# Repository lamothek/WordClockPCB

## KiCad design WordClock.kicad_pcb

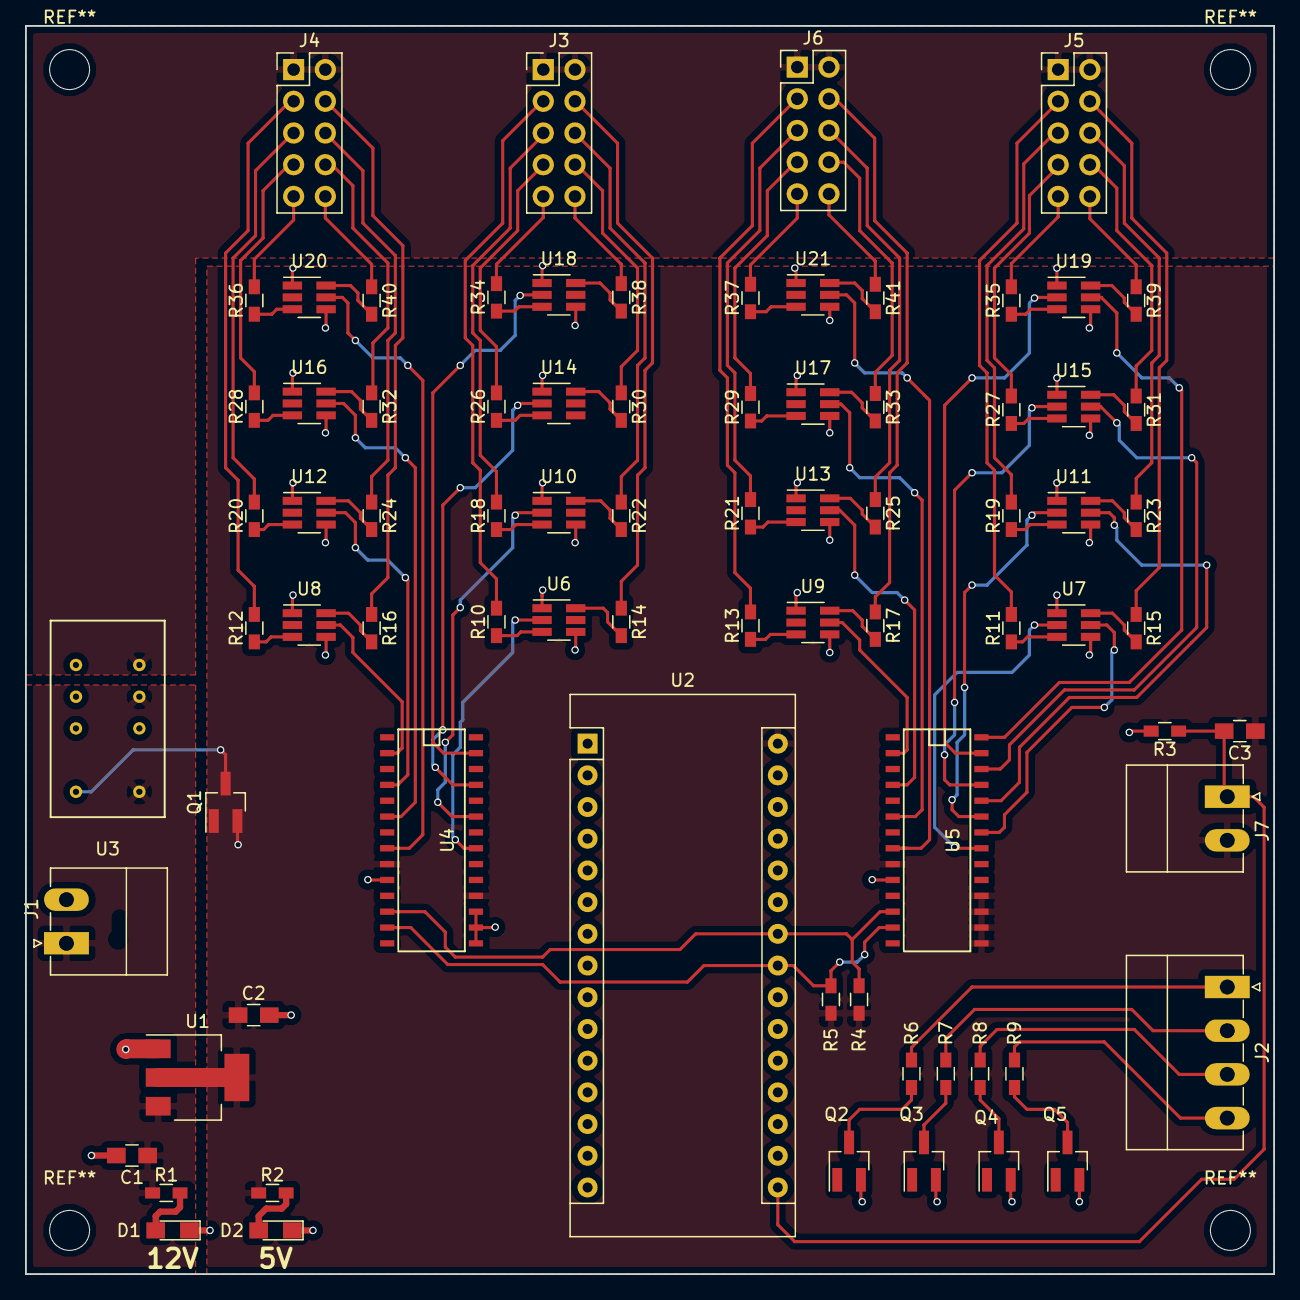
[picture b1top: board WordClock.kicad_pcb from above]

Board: 2 copper layers, 100.0 x 100.0 mm, 79 parts (0 on the bottom side), 119 nets.

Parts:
C1, C2: 4.7uF; C_0805_HandSoldering
C3: 100nF; C_0805_HandSoldering
D1, D2: LED; LED_0805_HandSoldering
J1, J7: Conn_01x02; PhoenixContact_MC-G_02x3.50mm_Angled
J2: Conn_01x04; PhoenixContact_MC-G_04x3.50mm_Angled
J3, J4, J5, J6: Conn_02x05_Top_Bottom; Pin_Header_Straight_2x05_Pitch2.54mm
Q1, Q2, Q3, Q4, Q5: Q_NMOS_GSD; SOT-23_Handsoldering
R1, R2: 1K; R_0603_HandSoldering
R3, R6, R7, R8, R9: 10K; R_0603_HandSoldering
R4, R5: 4.7K; R_0603_HandSoldering
R10, R11, R12, R13, R14, R15, R16, R17, R18, R19, R20, R21, R22, R23, R24, R25, R26, R27, R28, R29, R30, R31, R32, R33, R34, R35, R36, R37, R38, R39, R40, R41: 2.7K; R_0603_HandSoldering
U1: AP1117-50; SOT-223-3_TabPin2
U2: ARDUINO_NANO; Arduino_Nano
U3: E2C-12NU; EC2-12NU
U4, U5: MCP23017; SOIC-28
U6, U7, U8, U9, U10, U11, U12, U13, U14, U15, U16, U17, U18, U19, U20, U21: NUD3124; SOT-23-6_Handsoldering

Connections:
+5V: C2.1, C3.1, J7.2, R2.1, R4.1, R5.1, U1.2, U2.30, U4.9, U4.18, U5.9, U5.15, U5.16, U5.17, U5.18
+12V: C1.1, J1.1, R1.1, U1.3, U3.1, U3.4
ButtonRead: C3.2, J7.1, R3.1, U2.16
GND: C1.2, C2.2, D1.1, D2.1, J1.2, Q1.2, Q2.2, Q3.2, Q4.2, Q5.2, R3.2, U1.1, U2.4, U2.29, U4.10, U4.15, U4.16, U4.17, U5.10, U6.1, U6.4, U7.1, U7.4, U8.1, U8.4, U9.1, U9.4, U10.1, U10.4, U11.1, U11.4, U12.1, U12.4, U13.1, U13.4, U14.1, U14.4, U15.1, U15.4, U16.1, U16.4, U17.1, U17.4, U18.1, U18.4, U19.1, U19.4, U20.1, U20.4, U21.1, U21.4
LED1: J3.3, R10.2
LED2: J3.4, R14.1
LED3: J3.5, R18.2
LED4: J3.6, R22.1
LED5: J3.7, R26.2
LED6: J3.8, R30.1
LED7: J3.9, R34.2
LED8: J3.10, R38.1
LED9: J4.3, R12.2
LED10: J4.4, R16.1
LED11: J4.5, R20.2
LED12: J4.6, R24.1
LED13: J4.7, R28.2
LED14: J4.8, R32.1
LED15: J4.9, R36.2
LED16: J4.10, R40.1
LED17: J5.3, R11.2
LED18: J5.4, R15.1
LED19: J5.5, R19.2
LED20: J5.6, R23.1
LED21: J5.7, R27.2
LED22: J5.8, R31.1
LED23: J5.9, R35.2
LED24: J5.10, R39.1
LED25: J6.3, R13.2
LED26: J6.4, R17.1
LED27: J6.5, R21.2
LED28: J6.6, R25.1
LED29: J6.7, R29.2
LED30: J6.8, R33.1
LED31: J6.9, R37.2
LED32: J6.10, R41.1
LED_PWR: J3.1, J3.2, J4.1, J4.2, J5.1, J5.2, J6.1, J6.2, U3.5
unnamed: D1.2, R1.2
unnamed: D2.2, R2.2
unnamed: Q1.3, U3.12
unnamed: Q2.3, R6.2
unnamed: Q3.3, R7.2
unnamed: Q4.3, R8.2
unnamed: Q5.3, R9.2
unnamed: R10.1, U6.3
unnamed: R11.1, U7.3
unnamed: R12.1, U8.3
unnamed: R13.1, U9.3
unnamed: R14.2, U6.6
unnamed: R15.2, U7.6
unnamed: R16.2, U8.6
unnamed: R17.2, U9.6
unnamed: R18.1, U10.3
unnamed: R19.1, U11.3
unnamed: R20.1, U12.3
unnamed: R21.1, U13.3
unnamed: R22.2, U10.6
unnamed: R23.2, U11.6
unnamed: R24.2, U12.6
unnamed: R25.2, U13.6
unnamed: R26.1, U14.3
unnamed: R27.1, U15.3
unnamed: R28.1, U16.3
unnamed: R29.1, U17.3
unnamed: R30.2, U14.6
unnamed: R31.2, U15.6
unnamed: R32.2, U16.6
unnamed: R33.2, U17.6
unnamed: R34.1, U18.3
unnamed: R35.1, U19.3
unnamed: R36.1, U20.3
unnamed: R37.1, U21.3
unnamed: R38.2, U18.6
unnamed: R39.2, U19.6
unnamed: R40.2, U20.6
unnamed: R41.2, U21.6
OUT_1: U4.21, U6.2
OUT_2: U4.22, U6.5
OUT_3: U4.23, U10.2
OUT_4: U4.24, U10.5
OUT_5: U4.25, U14.2
OUT_6: U4.26, U14.5
OUT_7: U4.27, U18.2
OUT_8: U4.28, U18.5
OUT_9: U4.1, U8.2
OUT_10: U4.2, U8.5
OUT_11: U4.3, U12.2
OUT_12: U4.4, U12.5
OUT_13: U4.5, U16.2
OUT_14: U4.6, U16.5
OUT_15: U4.7, U20.2
OUT_16: U4.8, U20.5
OUT_17: U5.21, U7.2
OUT_18: U5.22, U7.5
OUT_19: U5.23, U11.2
OUT_20: U5.24, U11.5
OUT_21: U5.25, U15.2
OUT_22: U5.26, U15.5
OUT_23: U5.27, U19.2
OUT_24: U5.28, U19.5
OUT_25: U5.1, U9.2
OUT_26: U5.2, U9.5
OUT_27: U5.3, U13.2
OUT_28: U5.4, U13.5
OUT_29: U5.5, U17.2
OUT_30: U5.6, U17.5
OUT_31: U5.7, U21.2
OUT_32: U5.8, U21.5
PWM_1_CTRL: Q2.1, U2.6
PWM_1_OUTPUT: J2.1, R6.1
PWM_2_CTRL: Q3.1, U2.8
PWM_2_OUTPUT: J2.2, R7.1
PWM_3_CTRL: Q4.1, U2.9
PWM_3_OUTPUT: J2.3, R8.1
PWM_4_CTRL: Q5.1, U2.12
PWM_4_OUTPUT: J2.4, R9.1
RelayControl: Q1.1, U2.15
SCL: R4.2, U2.24, U4.12, U5.12
SDA: R5.2, U2.23, U4.13, U5.13

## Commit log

2017-10-17 Created arduino nano library for controls, no footprint yet. Created led-driver sheet for outputs from GPO to drive n-channel fets for low side driven control of led's
2017-10-19 Placed i2c labels and pull ups. Added 4 user input switches and MCP7940N RTC. Need to calculate capactiance for oscillator.
2017-10-25 Started assigning footprints. Much cheaper to use the two channel n-fet for led driving. Need to change schematic to reflec.
2017-10-27 Finished component footprint assignments and began rough layout of components.
2017-10-30 Routed power, clock, switches and started on arduino/IO expanders
2017-10-31 Continued with routing and board layout.
2017-11-02 Finished routing board.
2018-01-31 Started placing and routing new board with updated schematic. Requries RTC.
2018-02-02 Finished layout and began routing board.
2018-05-22 Fabriation files from first board spin. Footpring for IO expander incorrect, wide version used now, began board routing with new footprints.
